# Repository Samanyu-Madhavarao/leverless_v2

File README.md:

# leverless_v2
Wired arcade controller for PC, leverless style layout for fighting games

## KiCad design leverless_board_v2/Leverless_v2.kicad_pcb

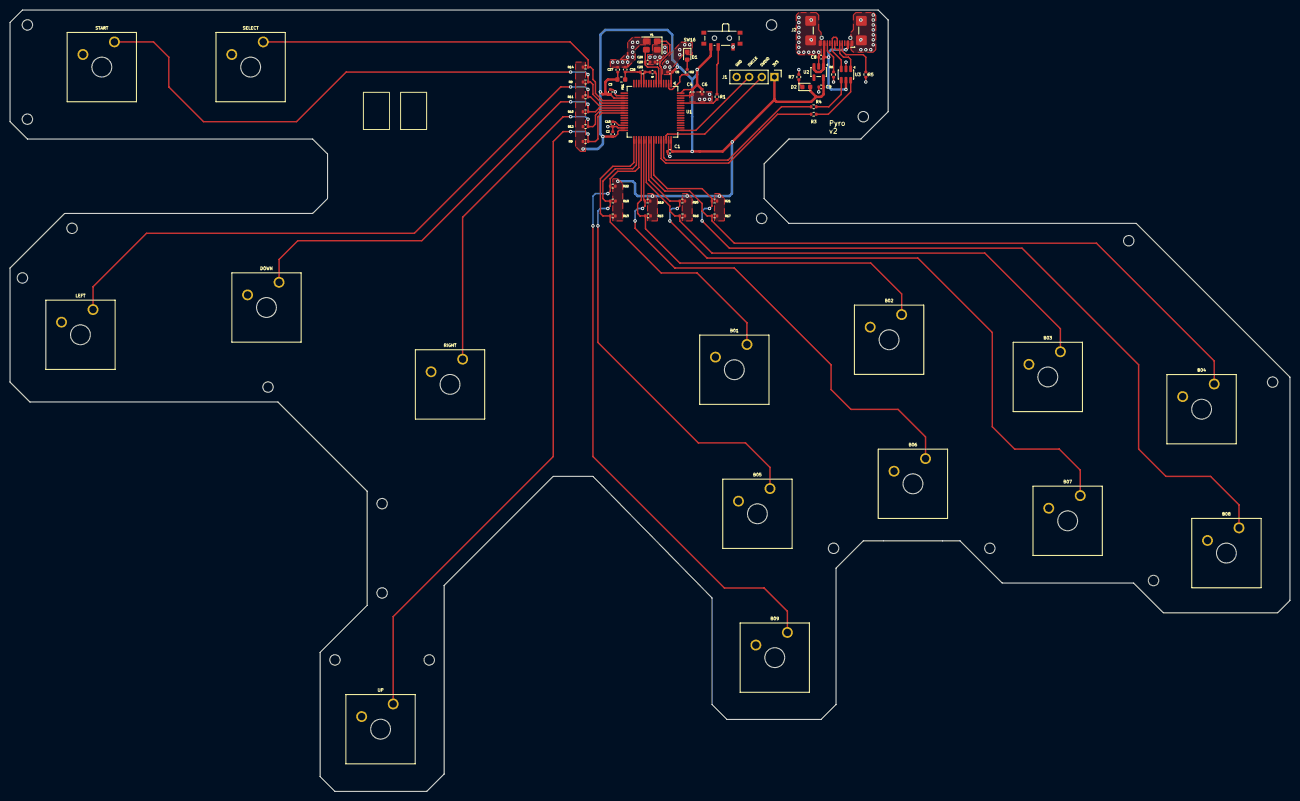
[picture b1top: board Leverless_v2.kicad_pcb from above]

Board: 2 copper layers, 258.0 x 157.5 mm, 62 parts (0 on the bottom side), 38 nets.

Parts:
B01: B01; SW_Cherry_MX_1.00u_Plate
B02: B02; SW_Cherry_MX_1.00u_Plate
B03: B03; SW_Cherry_MX_1.00u_Plate
B04: B04; SW_Cherry_MX_1.00u_Plate
B05: B05; SW_Cherry_MX_1.00u_Plate
B06: B06; SW_Cherry_MX_1.00u_Plate
B07: B07; SW_Cherry_MX_1.00u_Plate
B08: B08; SW_Cherry_MX_1.00u_Plate
B09: B09; SW_Cherry_MX_1.00u_Plate
C1, C2, C3, C4, C5, C7: 100nF; C_0402_1005Metric
C6: 4.7uF; C_0402_1005Metric
C8, C9, C26, C27: 1uF; C_0402_1005Metric
C10: 2.2uF; C_0402_1005Metric
C25: 10nF; C_0402_1005Metric
C28, C29: 10pF; C_0402_1005Metric
D1: DEBUG_LED; LED_0603_1608Metric
D2: RED; LED_0603_1608Metric
DOWN: DOWN; SW_Cherry_MX_1.00u_Plate
FB1: 120R; L_0603_1608Metric
J1: Conn_01x04; PinHeader_1x04_P2.54mm_Vertical
J2: USB_C_Receptacle_USB2.0_16P; USB_C_Receptacle_GCT_USB4110
LEFT: LEFT; SW_Cherry_MX_1.00u_Plate
R1, R8, R9, R10, R11, R12, R13, R14, R15, R16, R17, R18, R19, R20, R21, R22: 10k; R_0402_1005Metric
R2, R7: 510; R_0402_1005Metric
R3, R4: 22; R_0402_1005Metric
R5, R6: 5.1k; R_0402_1005Metric
RIGHT: RIGHT; SW_Cherry_MX_1.00u_Plate
SELECT: SELECT; SW_Cherry_MX_1.00u_Plate
START: START; SW_Cherry_MX_1.00u_Plate
SW16: SW_SPDT; SW_SPDT_PCM12
U1: STM32F411RCTx; LQFP-64_10x10mm_P0.5mm
U2: AP2112K-3.3; SOT-23-5
U3: USBLC6-2SC6; SOT-23-6
UP: UP; SW_Cherry_MX_1.00u_Plate
Y1: 16MHz; Crystal_SMD_3225-4Pin_3.2x2.5mm

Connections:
3V3: C1.1, C2.1, C3.1, C4.1, C5.1, C6.1, C9.1, C27.1, D2.2 (A), FB1.2, J1.1, R8.2, R9.2, R10.2, R11.2, R12.2, R13.2, R14.2, R15.2, R16.2, R17.2, R18.2, R19.2, R20.2, R21.2, R22.2, SW16.3 (C), U1.1 (VBAT), U1.19 (VDD), U1.32 (VDD), U1.48 (VDD), U1.64 (VDD), U2.5 (VOUT)
3V3A: C25.1, C26.1, FB1.1, U1.13 (VDDA)
/BOOT0: R1.2, U1.60 (BOOT0)
/NRST: C7.2, U1.7 (NRST)
/PWR_LED_K: D2.1 (K), R7.1
B01: B01.1, R13.1, U1.33 (PB12)
B02: B02.1, R15.1, U1.36 (PB15)
B03: B03.1, R16.1, U1.38 (PC7)
B04: B04.1, R17.1, U1.40 (PC9)
B05: B05.1, R18.1, U1.34 (PB13)
B06: B06.1, R19.1, U1.37 (PC6)
B07: B07.1, R20.1, U1.39 (PC8)
B08: B08.1, R21.1, U1.41 (PA8)
B09: B09.1, R22.1, U1.35 (PB14)
DOWN: DOWN.1, R10.1, U1.23 (PA7)
GND: B01.2, B02.2, B03.2, B04.2, B05.2, B06.2, B07.2, B08.2, B09.2, C1.2, C2.2, C3.2, C4.2, C5.2, C6.2, C7.1, C8.2, C9.2, C10.2, C25.2, C26.2, C27.2, C28.2, C29.2, D1.1 (K), DOWN.2, J1.4, J2.A1 (GND), J2.A12 (GND), J2.B1 (GND), J2.B12 (GND), J2.S1 (SHIELD), LEFT.2, R5.2, R6.2, R7.2, RIGHT.2, SELECT.2, START.2, SW16.1 (A), U1.12 (VSSA), U1.18 (VSS), U1.31 (VSS), U1.47 (VSS), U1.63 (VSS), U2.2 (GND), U3.2 (GND), UP.2, Y1.2, Y1.4
LEFT: LEFT.1, R11.1, U1.22 (PA6)
unnamed: D1.2 (A), R2.1
unnamed: J2.A5 (CC1), R5.1
unnamed: J2.B5 (CC2), R6.1
unnamed: J2.A6 (D+), J2.B6 (D+), U3.3 (I/O2)
unnamed: J2.A7 (D-), J2.B7 (D-), U3.1 (I/O1)
unnamed: R3.1, U3.6 (I/O1)
unnamed: R4.1, U3.4 (I/O2)
unnamed: R1.1, SW16.2 (B)
unnamed: R2.2, U1.2 (PC13)
unnamed: C28.1, U1.5 (PH0), Y1.1
unnamed: C29.1, U1.6 (PH1), Y1.3
unnamed: C10.1, U1.30 (VCAP1)
RIGHT: R12.1, RIGHT.1, U1.24 (PC4)
SELECT: R14.1, SELECT.1, U1.20 (PA4)
START: R8.1, START.1, U1.21 (PA5)
SWCLK: J1.3, U1.49 (PA14)
SWDIO: J1.2, U1.46 (PA13)
UP: R9.1, U1.25 (PC5), UP.1
USB_DM: R3.2, U1.44 (PA11)
USB_DP: R4.2, U1.45 (PA12)
VBUS: C8.1, J2.A4 (VBUS), J2.A9 (VBUS), J2.B4 (VBUS), J2.B9 (VBUS), U2.1 (VIN), U2.3 (EN), U3.5 (VBUS)

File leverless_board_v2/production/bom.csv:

Designator,Footprint,Quantity,Value,LCSC Part #
"01, 02, 03, 04, 05, 06, 07, 08, 09, D, L, R, R1, SE, ST, U",0402,16,10k,
B01,SW_Cherry_MX_1.00u_Plate,1,B01,
B02,SW_Cherry_MX_1.00u_Plate,1,B02,
B03,SW_Cherry_MX_1.00u_Plate,1,B03,
B04,SW_Cherry_MX_1.00u_Plate,1,B04,
B05,SW_Cherry_MX_1.00u_Plate,1,B05,
B06,SW_Cherry_MX_1.00u_Plate,1,B06,
B07,SW_Cherry_MX_1.00u_Plate,1,B07,
B08,SW_Cherry_MX_1.00u_Plate,1,B08,
B09,SW_Cherry_MX_1.00u_Plate,1,B09,
"C1, C2, C3, C4, C5, C7",0402,6,100nF,
C10,0402,1,2.2uF,
C25,0402,1,10nF,
"C26, C27, C8, C9",0402,4,1uF,
"C28, C29",0402,2,10pF,
C6,0402,1,4.7uF,
D1,0603,1,DEBUG_LED,
D2,0603,1,RED,
DOWN,SW_Cherry_MX_1.00u_Plate,1,DOWN,
FB1,0603,1,120R,
J1,PinHeader_1x04_P2.54mm_Vertical,1,Conn_01x04,
J2,USB_C_Receptacle_GCT_USB4110,1,USB_C_Receptacle_USB2.0_16P,
LEFT,SW_Cherry_MX_1.00u_Plate,1,LEFT,
"R2, R7",0402,2,510,
"R3, R4",0402,2,22,
"R5, R6",0402,2,5.1k,
RIGHT,SW_Cherry_MX_1.00u_Plate,1,RIGHT,
SELECT,SW_Cherry_MX_1.00u_Plate,1,SELECT,
START,SW_Cherry_MX_1.00u_Plate,1,START,
SW16,SW_SPDT_PCM12,1,SW_SPDT,
U1,LQFP-64_10x10mm_P0.5mm,1,STM32F411RCTx,
U2,SOT-23-5,1,AP2112K-3.3,
U3,SOT-23-6,1,USBLC6-2SC6,
UP,SW_Cherry_MX_1.00u_Plate,1,UP,
Y1,Crystal_SMD_3225-4Pin_3.2x2.5mm,1,16MHz,

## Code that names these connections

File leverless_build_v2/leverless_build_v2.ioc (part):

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Mcu.Name=STM32F411R(C-E)Tx
Mcu.Package=LQFP64
Mcu.UserName=STM32F411RCTx
PA11.Mode=Device_Only
PA11.Signal=USB_OTG_FS_DM
PA12.Mode=Device_Only
PA12.Signal=USB_OTG_FS_DP
PA13.Mode=Serial_Wire
PA13.Signal=SYS_JTMS-SWDIO
PA14.Mode=Serial_Wire
PA14.Signal=SYS_JTCK-SWCLK
PA4.GPIOParameters=GPIO_Label
PA4.GPIO_Label=SELECT
PA4.Signal=GPIO_Input
PA5.GPIOParameters=GPIO_Label
PA5.GPIO_Label=START
PA5.Signal=GPIO_Input
PA6.GPIOParameters=GPIO_Label
PA6.GPIO_Label=LEFT
PA6.Signal=GPIO_Input
PA7.GPIOParameters=GPIO_Label
PA7.GPIO_Label=DOWN
PA7.Signal=GPIO_Input
PA8.GPIOParameters=GPIO_Label
PA8.GPIO_Label=B08
PA8.Signal=GPIO_Input
PB12.GPIOParameters=GPIO_Label
PB12.GPIO_Label=B01
PB12.Signal=GPIO_Input
PB13.GPIOParameters=GPIO_Label
PB13.GPIO_Label=B05
PB13.Signal=GPIO_Input
PB14.GPIOParameters=GPIO_Label
PB14.GPIO_Label=B09
PB14.Signal=GPIO_Input
PB15.GPIOParameters=GPIO_Label
PB15.GPIO_Label=B02
PB15.Signal=GPIO_Input
PC4.GPIOParameters=GPIO_Label
PC4.GPIO_Label=RIGHT
PC4.Signal=GPIO_Input
PC5.GPIOParameters=GPIO_Label
PC5.GPIO_Label=UP
PC5.Signal=GPIO_Input
PC6.GPIOParameters=GPIO_Label
PC6.GPIO_Label=B06
PC6.Signal=GPIO_Input
PC7.GPIOParameters=GPIO_Label
PC7.GPIO_Label=B03
PC7.Signal=GPIO_Input
PC8.GPIOParameters=GPIO_Label
PC8.GPIO_Label=B07
PC8.Signal=GPIO_Input
PC9.GPIOParameters=GPIO_Label
PC9.GPIO_Label=B04
PC9.Signal=GPIO_Input
PH0\ -\ OSC_IN.Mode=HSE-External-Oscillator
PH0\ -\ OSC_IN.Signal=RCC_OSC_IN
PH1\ -\ OSC_OUT.Mode=HSE-External-Oscillator
PH1\ -\ OSC_OUT.Signal=RCC_OSC_OUT
RCC.HSE_VALUE=16000000
RCC.SYSCLKFreq_VALUE=96000000
RCC.SYSCLKSource=RCC_SYSCLKSOURCE_PLLCLK
board=custom
